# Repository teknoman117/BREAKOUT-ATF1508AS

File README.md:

# BREAKOUT-ATF1508AS

A breakout board for the PLCC84 version of the ATF1504AS or ATF1508AS. Allows for usage in a breadboard environment.

### Example Project

See 

### Dual Voltage Rails

The PLCC84 variants of the ATF1504AS and ATF1504AS provide two voltage rails - VCCINT and VCCIO. VCCINT is the CPLD core voltage and is required to be at 5V. VCCIO is the external IO voltage and can be either 3.3V (3.0V to 3.6V) or 5V.

### Oscillator

Socket X1 is for a 3.3V or 5V TTL oscillator in the 4 lead DIP-8 form factor. The enable pin is left electrically unconnected, which is enabled for the majority of TTL oscillators. 

The oscillator output is connected to I83/GCLK1. If an external clock is provided on I83/GCLK1 through the breakout headers, the oscillator must be removed.

Jumper JP1 selects the source voltage of the oscillator. Position 1-2 connects the oscillator to the VCCIO rail and Position 2-3 connects to the VCCINT (5V) rail.

### Programming

In the event that JTAG has been disabled on the CPLD, a 12V boost regulator is provided to force the CPLD into JTAG mode.

Jumper JP2 selects the function of the I84/OE1 pin. Position 1-2 is normal operation, with the pin connected to the breakout headers along the bottom of the board. Position 2-3 is for erase. This disconnects the pin from the breakout headers and instead connects it to 12V through current limiting resistor R3 (2.2 kOhm by default).

Programming can be achieved with an official programmer or a FT232H and OpenOCD. See 

Please note that JTAG Header J1 is not isolated from the breakout headers. If the design uses P14 (TDI), P23 (TMS), P62 (TCK), or P71 (TDO), the breakout board may need to be removed from the circuit prior to programming.

### Errata

The I2/GCLK2 label on the breakout headers should be I2/GCLK2/OE2.

### License

CC-BY-SA 4.0

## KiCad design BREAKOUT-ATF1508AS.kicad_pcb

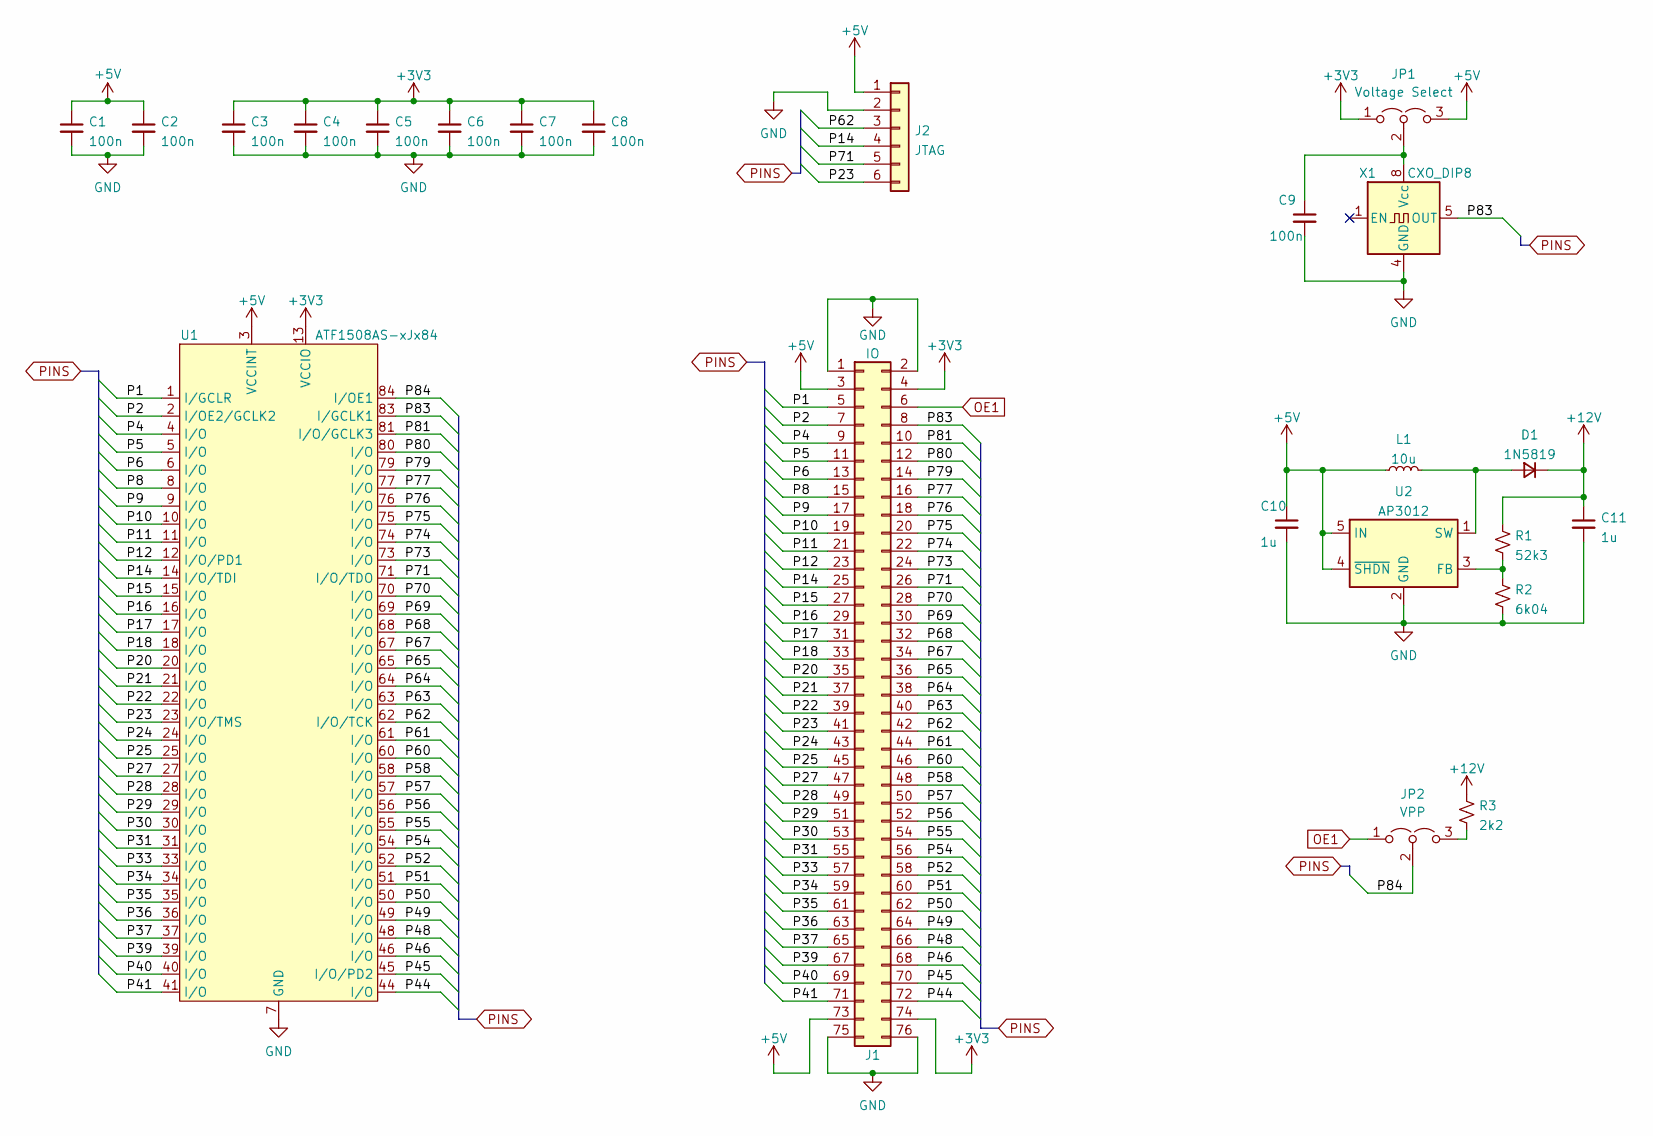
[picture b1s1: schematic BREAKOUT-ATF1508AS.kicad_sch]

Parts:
C1, C2, C3, C4, C5, C6, C7, C8, C9: 100n; C_0603_1608Metric_Pad1.08x0.95mm_HandSolder
C10, C11: 1u; C_0603_1608Metric_Pad1.08x0.95mm_HandSolder
D1: 1N5819; D_SOD-323_HandSoldering
J1: IO; PinHeader_2x38_P2.54mm_Vertical
J2: JTAG; PinHeader_1x06_P2.54mm_Vertical
JP1: Voltage Select; PinHeader_1x03_P2.54mm_Vertical
JP2: VPP; PinHeader_1x03_P2.54mm_Vertical
L1: 10u; L_1008_2520Metric_Pad1.43x2.20mm_HandSolder
R1: 52k3; R_0603_1608Metric_Pad0.98x0.95mm_HandSolder
R2: 6k04; R_0603_1608Metric_Pad0.98x0.95mm_HandSolder
R3: 2k2; R_0603_1608Metric_Pad0.98x0.95mm_HandSolder
U1: ATF1508AS-xJx84; PLCC-84_THT-Socket
U2: AP3012; SOT-23-5
X1: CXO_DIP8; Oscillator_DIP-8

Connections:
+3V3: C3.1, C4.1, C5.1, C6.1, C7.1, C8.1, J1.4, J1.74, JP1.1 (A), U1.13 (VCCIO), U1.26 (VCCIO), U1.38 (VCCIO), U1.53 (VCCIO), U1.66 (VCCIO), U1.78 (VCCIO)
+5V: C1.1, C2.1, C10.1, J1.3, J1.73, J2.1, JP1.3 (B), L1.1, U1.3 (VCCINT), U1.43 (VCCINT), U2.4 (~SHDN), U2.5 (IN)
+12V: C11.1, D1.1 (K), R1.1, R3.1
/P1: J1.5, U1.1 (I/GCLR)
/P2: J1.7, U1.2 (I/OE2/GCLK2)
/P4: J1.9, U1.4 (I/O)
/P5: J1.11, U1.5 (I/O)
/P6: J1.13, U1.6 (I/O)
/P8: J1.15, U1.8 (I/O)
/P9: J1.17, U1.9 (I/O)
/P10: J1.19, U1.10 (I/O)
/P11: J1.21, U1.11 (I/O)
/P12: J1.23, U1.12 (I/O/PD1)
/P14: J1.25, J2.4, U1.14 (I/O/TDI)
/P15: J1.27, U1.15 (I/O)
/P16: J1.29, U1.16 (I/O)
/P17: J1.31, U1.17 (I/O)
/P18: J1.33, U1.18 (I/O)
/P20: J1.35, U1.20 (I/O)
/P21: J1.37, U1.21 (I/O)
/P22: J1.39, U1.22 (I/O)
/P23: J1.41, J2.6, U1.23 (I/O/TMS)
/P24: J1.43, U1.24 (I/O)
/P25: J1.45, U1.25 (I/O)
/P27: J1.47, U1.27 (I/O)
/P28: J1.49, U1.28 (I/O)
/P29: J1.51, U1.29 (I/O)
/P30: J1.53, U1.30 (I/O)
/P31: J1.55, U1.31 (I/O)
/P33: J1.57, U1.33 (I/O)
/P34: J1.59, U1.34 (I/O)
/P35: J1.61, U1.35 (I/O)
/P36: J1.63, U1.36 (I/O)
/P37: J1.65, U1.37 (I/O)
/P39: J1.67, U1.39 (I/O)
/P40: J1.69, U1.40 (I/O)
/P41: J1.71, U1.41 (I/O)
/P44: J1.72, U1.44 (I/O)
/P45: J1.70, U1.45 (I/O/PD2)
/P46: J1.68, U1.46 (I/O)
/P48: J1.66, U1.48 (I/O)
/P49: J1.64, U1.49 (I/O)
/P50: J1.62, U1.50 (I/O)
/P51: J1.60, U1.51 (I/O)
/P52: J1.58, U1.52 (I/O)
/P54: J1.56, U1.54 (I/O)
/P55: J1.54, U1.55 (I/O)
/P56: J1.52, U1.56 (I/O)
/P57: J1.50, U1.57 (I/O)
/P58: J1.48, U1.58 (I/O)
/P60: J1.46, U1.60 (I/O)
/P61: J1.44, U1.61 (I/O)
/P62: J1.42, J2.3, U1.62 (I/O/TCK)
/P63: J1.40, U1.63 (I/O)
/P64: J1.38, U1.64 (I/O)
/P65: J1.36, U1.65 (I/O)
/P67: J1.34, U1.67 (I/O)
/P68: J1.32, U1.68 (I/O)
/P69: J1.30, U1.69 (I/O)
/P70: J1.28, U1.70 (I/O)
/P71: J1.26, J2.5, U1.71 (I/O/TDO)
/P73: J1.24, U1.73 (I/O)
/P74: J1.22, U1.74 (I/O)
/P75: J1.20, U1.75 (I/O)
/P76: J1.18, U1.76 (I/O)
/P77: J1.16, U1.77 (I/O)
/P79: J1.14, U1.79 (I/O)
/P80: J1.12, U1.80 (I/O)
/P81: J1.10, U1.81 (I/O/GCLK3)
/P83: J1.8, U1.83 (I/GCLK1), X1.5 (OUT)
/P84: JP2.2 (C), U1.84 (I/OE1)
GND: C1.2, C2.2, C3.2, C4.2, C5.2, C6.2, C7.2, C8.2, C9.2, C10.2, C11.2, J1.1, J1.2, J1.75, J1.76, J2.2, R2.2, U1.7 (GND), U1.19 (GND), U1.32 (GND), U1.42 (GND), U1.47 (GND), U1.59 (GND), U1.72 (GND), U1.82 (GND), U2.2 (GND), X1.4 (GND)
unnamed: C9.1, JP1.2 (C), X1.8 (Vcc)
unnamed: D1.2 (A), L1.2, U2.1 (SW)
unnamed: JP2.3 (B), R3.2
unnamed: R1.2, R2.1, U2.3 (FB)
OE1: J1.6, JP2.1 (A)

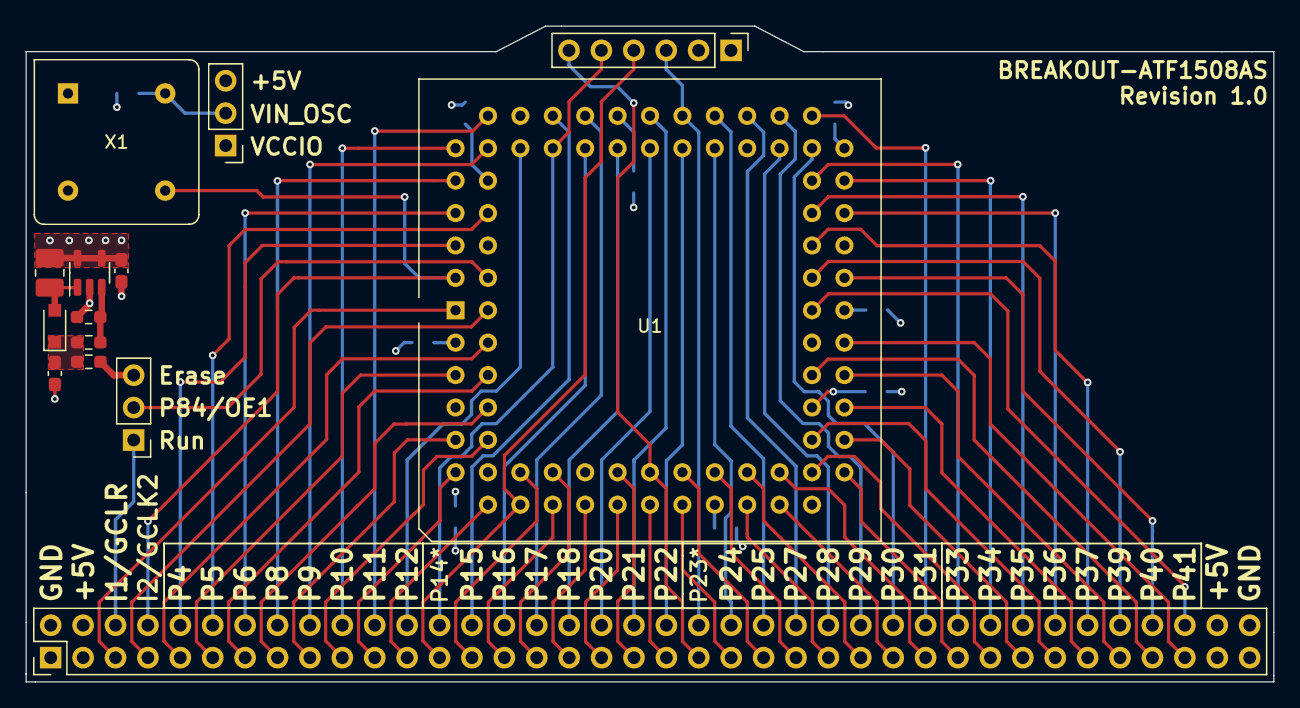
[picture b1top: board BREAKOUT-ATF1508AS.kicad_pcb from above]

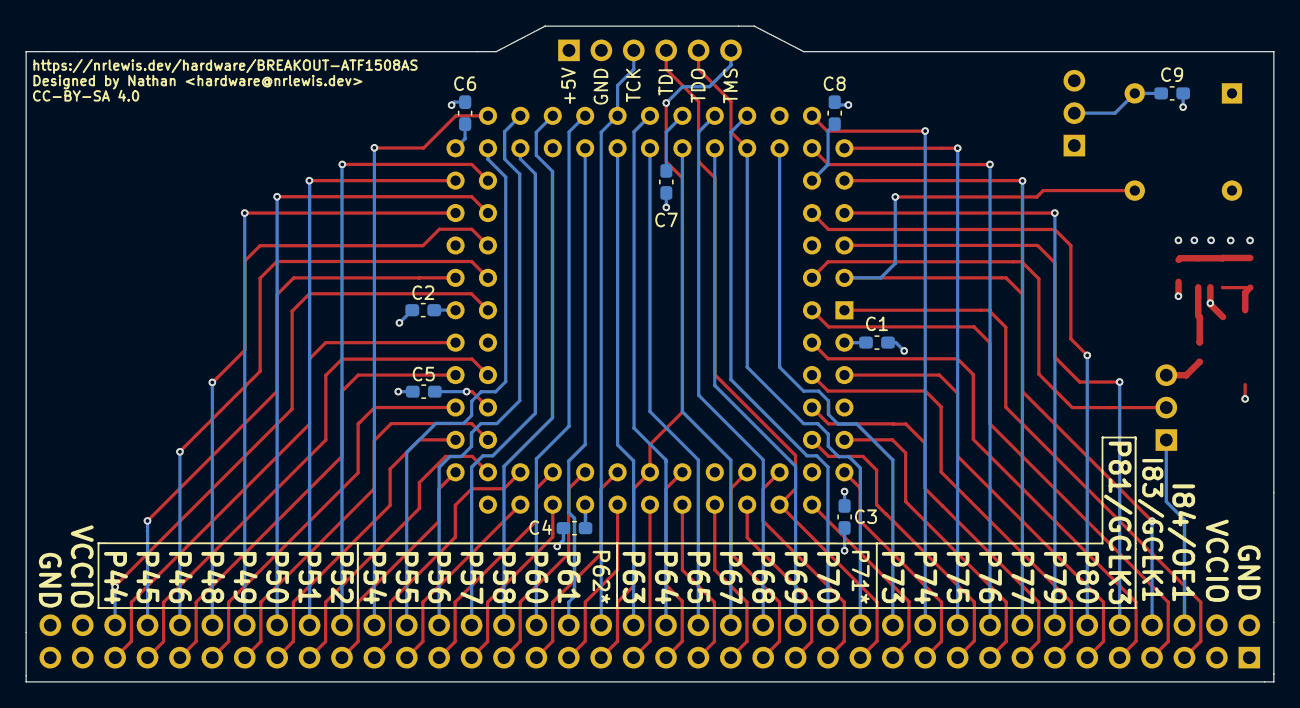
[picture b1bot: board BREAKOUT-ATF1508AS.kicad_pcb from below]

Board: 4 copper layers, 97.8 x 51.4 mm, 23 parts (9 on the bottom side), 77 nets.

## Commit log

2025-04-29 add demo
